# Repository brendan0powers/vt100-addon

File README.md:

vt100-addon
===========

STP add-on board for the VT100 series terminals that allows the use of an internal BeageBone instead of an external serial connected computer.

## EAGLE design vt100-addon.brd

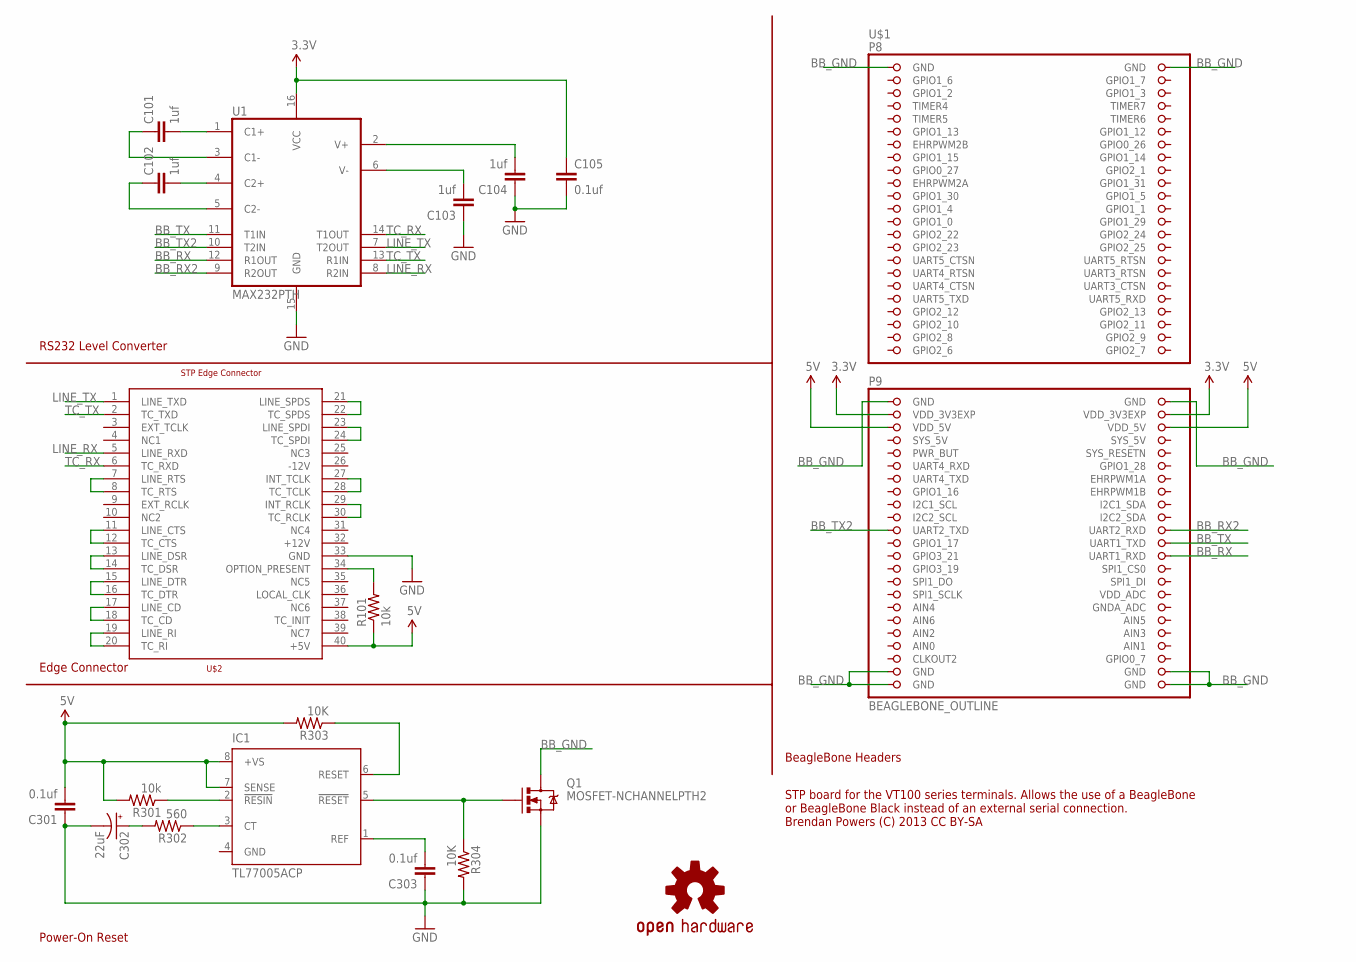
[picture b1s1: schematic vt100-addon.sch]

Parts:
C101, C102, C103, C104: 1uf; CAP-PTH-SMALL
C105, C301, C303: 0.1uf; CAP-PTH-SMALL
C302: 22uF; CPOL-RADIAL-100UF-25V
IC1: TL77005ACP; DIL08
Q1: MOSFET-NCHANNELPTH2; TO220V
R101, R301: 10k; AXIAL-0.4
R302: 560; AXIAL-0.4
R303, R304: 10K; AXIAL-0.4
U1: MAX232PTH; DIL16
U$1: BEAGLEBONE_OUTLINE; BEAGLEBONE_SHIELD
U$2: STP_EDGE
U$7: OSHW-LOGOL; OSHW-LOGO-L

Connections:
3.3V: C105.1, U1.16 (VCC), U$1.49 (VDD_3V3EXP), U$1.50 (VDD_3V3EXP)
5V: C301.2, IC1.7 (SENSE), IC1.8 (+VS), R101.P$1 (1), R301.P$2 (2), R303.P$2 (2), U$1.51 (VDD_5V), U$1.52 (VDD_5V), U$2.40 (+5V)
AIN0: U$1.85 (AIN0)
BB_GND: Q1.2 (D), U$1.1 (GND), U$1.2 (GND), U$1.47 (GND), U$1.48 (GND), U$1.89 (GND), U$1.90 (GND), U$1.91 (GND), U$1.92 (GND)
BB_RX: U1.12 (R1OUT), U$1.72 (UART1_RXD)
BB_RX2: U1.9 (R2OUT), U$1.68 (UART2_RXD)
BB_TX: U1.11 (T1IN), U$1.70 (UART1_TXD)
BB_TX2: U1.10 (T2IN), U$1.67 (UART2_TXD)
GND: C103.1, C104.1, C105.2, C301.1, C302.2 (-), C303.1, IC1.4 (GND), Q1.3 (S), R304.P$2 (2), U1.15 (GND), U$2.33 (GND)
LINE_RX: U1.8 (R2IN), U$2.5 (LINE_RXD)
LINE_TX: U1.7 (T2OUT), U$2.1 (LINE_TXD)
unnamed: C101.2, U1.1 (C1+)
unnamed: C101.1, U1.3 (C1-)
unnamed: C102.2, U1.4 (C2+)
unnamed: C102.1, U1.5 (C2-)
unnamed: R101.P$2 (2), U$2.34 (OPTION_PRESENT)
unnamed: C104.2, U1.2 (V+)
unnamed: C103.2, U1.6 (V-)
unnamed: U$2.7 (LINE_RTS), U$2.8 (TC_RTS)
unnamed: U$2.11 (LINE_CTS), U$2.12 (TC_CTS)
unnamed: U$2.13 (LINE_DSR), U$2.14 (TC_DSR)
unnamed: U$2.15 (LINE_DTR), U$2.16 (TC_DTR)
unnamed: U$2.17 (LINE_CD), U$2.18 (TC_CD)
unnamed: U$2.19 (LINE_RI), U$2.20 (TC_RI)
unnamed: U$2.21 (LINE_SPDS), U$2.22 (TC_SPDS)
unnamed: U$2.23 (LINE_SPDI), U$2.24 (TC_SPDI)
unnamed: U$2.27 (INT_TCLK), U$2.28 (TC_TCLK)
unnamed: U$2.29 (INT_RCLK), U$2.30 (TC_RCLK)
unnamed: IC1.3 (CT), R302.P$1 (1)
unnamed: C303.2, IC1.1 (REF)
unnamed: C302.1 (+), R302.P$2 (2)
unnamed: IC1.6 (RESET), R303.P$1 (1)
unnamed: IC1.5 (!RESET), Q1.1 (G), R304.P$1 (1)
unnamed: IC1.2 (!RESIN), R301.P$1 (1)
SYS_5V: U$1.53 (SYS_5V)
TC_RX: U1.14 (T1OUT), U$2.6 (TC_RXD)
TC_TX: U1.13 (R1IN), U$2.2 (TC_TXD)

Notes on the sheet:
RS232 Level Converter
Edge Connector
Power-On Reset
BeagleBone Headers
STP board for the VT100 series terminals. Allows the use of a BeagleBone or BeagleBone Black instead of an external serial connection. Brendan Powers (C) 2013 CC BY-SA

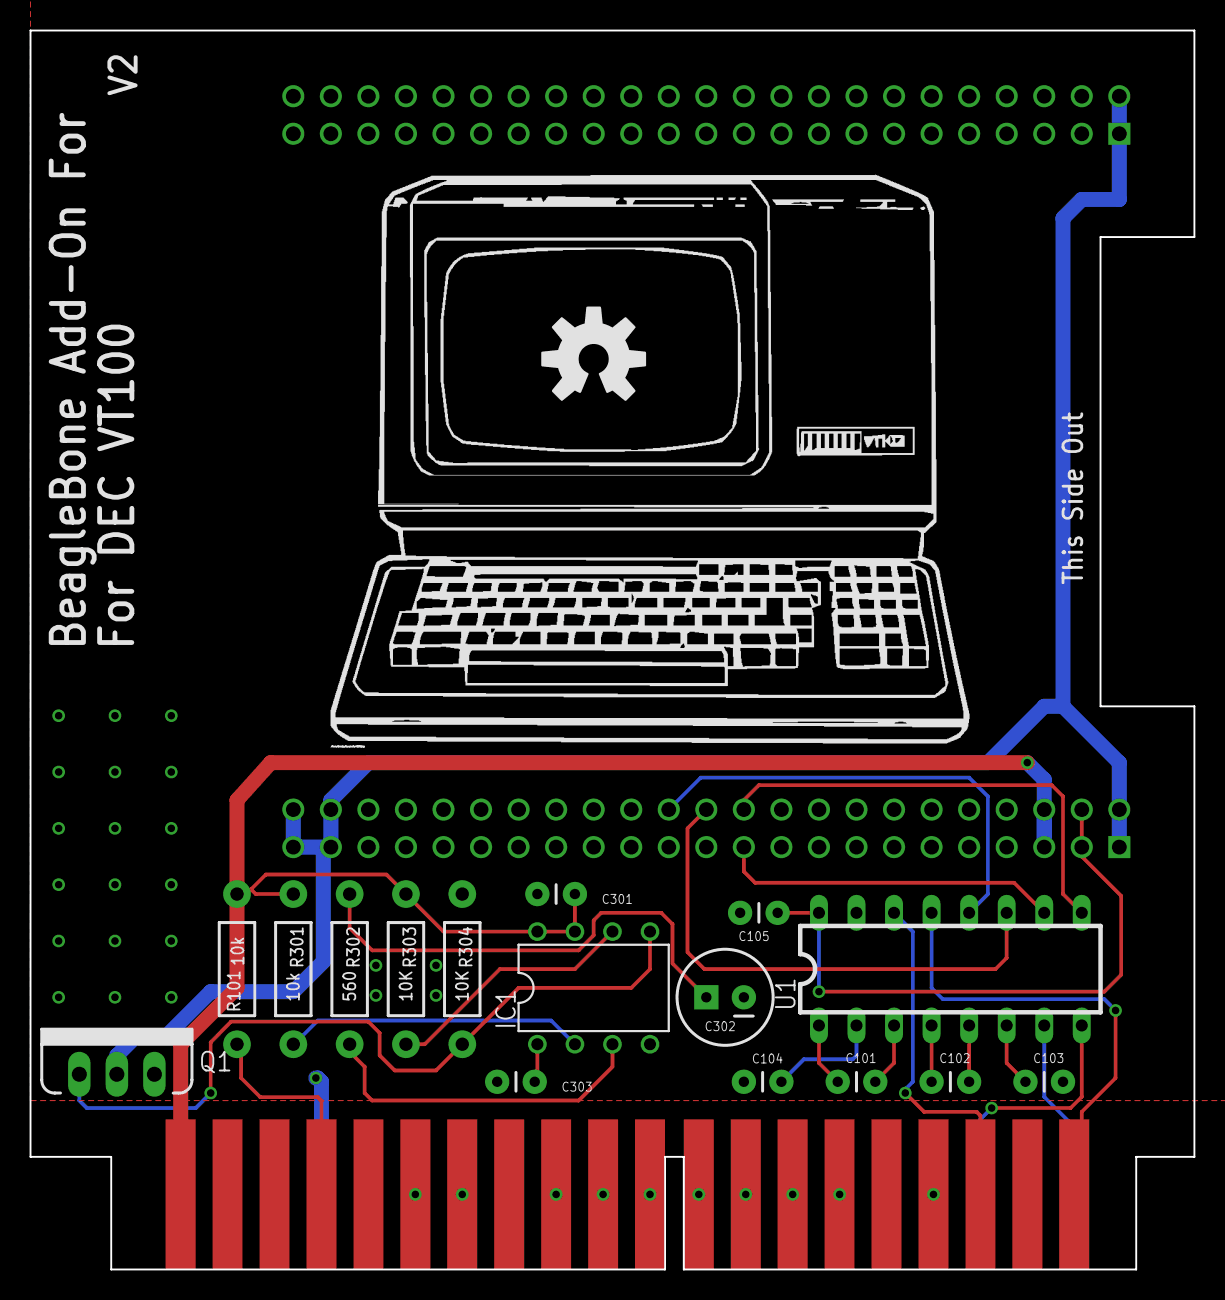
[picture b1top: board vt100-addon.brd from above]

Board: 2 copper layers, 78.7 x 83.8 mm, 19 parts (1 on the bottom side), 35 nets.

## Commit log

2013-08-25 Added V2 of the board
2013-08-25 Removed git backup file and added a gitignore file
2013-08-25 More board refinements
2013-08-29 A bit more cleanup
2015-01-05 Create README.md
    Added uic library service add on

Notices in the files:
parts and their libraries:
sparkfun: Licensing: CC v3.0 Share-Alike You are welcome to use this library for commercial purposes.
